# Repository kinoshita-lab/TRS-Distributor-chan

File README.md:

# TRS Distributor chan

[Document in Japanese](README_ja.md)

TRS Distributor chan is a passive, battery free utility PCB to distribute/merge TRS signals such as KORG sync, audio etc.
It would be useful for some situations in your musical life, for example syncing multiple devices without cascading.

## Usage

All of the I/Os are created equal.
If you input signal from one of the I/O, then it goes to all of the other I/O terminals via resistors.

If you input signals from multiple I/Os, they will be mixed you can obtain it from other terminals via resistors.

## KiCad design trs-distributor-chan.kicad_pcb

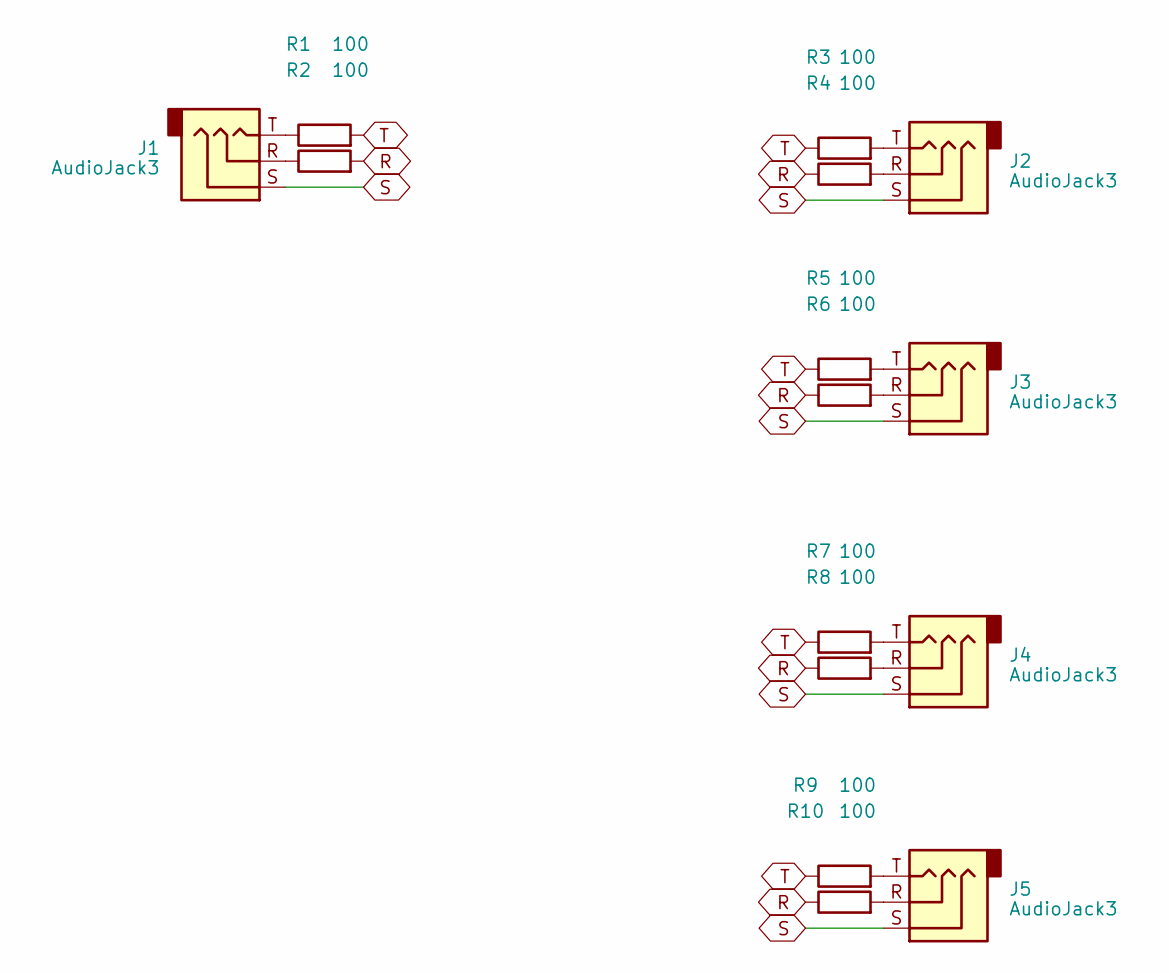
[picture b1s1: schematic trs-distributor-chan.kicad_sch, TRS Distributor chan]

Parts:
J1, J2, J3, J4, J5: AudioJack3; AudioJack_3.5mm_TRS_SMD_C18594; LCSC C18594
R1, R2, R3, R4, R5, R6, R7, R8, R9, R10: 100; R_0603_1608Metric_Pad0.98x0.95mm_HandSolder; LCSC C844724

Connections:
unnamed: J1.R, R2.1
unnamed: J1.T, R1.1
unnamed: J2.R, R4.2
unnamed: J2.T, R3.2
unnamed: J3.R, R6.2
unnamed: J3.T, R5.2
unnamed: J4.R, R8.2
unnamed: J4.T, R7.2
unnamed: J5.R, R10.2
unnamed: J5.T, R9.2
R: R2.2, R4.1, R6.1, R8.1, R10.1
S: J1.S, J2.S, J3.S, J4.S, J5.S
T: R1.2, R3.1, R5.1, R7.1, R9.1

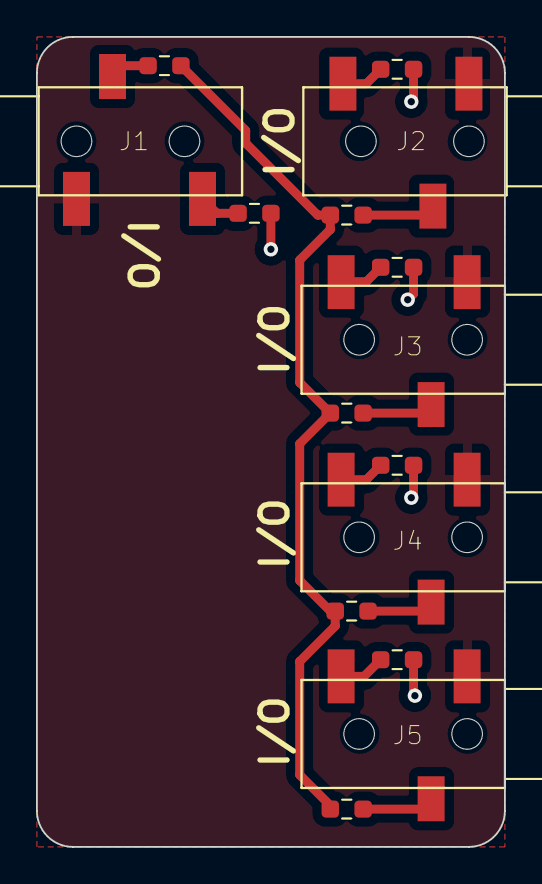
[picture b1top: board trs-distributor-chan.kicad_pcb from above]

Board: 2 copper layers, 26.0 x 45.0 mm, 15 parts (0 on the bottom side), 13 nets.

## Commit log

2024-01-23 Create LICENSE
2024-01-23 add files
